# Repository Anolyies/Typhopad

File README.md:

# Typhopad
A Starter Hackpad Project | By Anolyies

**A Short Rant**
I used Solidworks rather than Fusion360, the assembly part of the case was really annoying, I didn't know what to do, and the tutorials online weren't great, but I got it done alright, I think. Also, colors in the images look terible, because I added them last second.

The Schematic / PCB:
-------------------------------
   
*Schematic / Left*                                              | *PCB / Right*

--------------------------------------------------
I wasn't too sure on how to make the PCB. It's my first time using KICad and making a PCB schematic. The routing and pcb itself looks pretty bad, it doesn't use a switch matrix, it's directly wired. I'm not too sure what that means but yeah. I tried to follow the beginner friendly tutorial as close as possible, then added the OLED display and RotaryEncoder, but kind of winged it, as there was no tutorial on how to do those ones. I don't know if this PCB will work, but I hope it will. Lastly, the OLED display area, I'll just directly solder the pins on the OLED display into the holes rather than using a JConnector.

The Assembly:
----------------------------------

---------------------------------------------
This design follows the tutorial really pretty closely with only a few differences, but I think that's fine for a semi-beginner.

I add the PCB with wiring,soldering, and etc... Into the bottom case. 4x M3x16mm screws go through the bottom of the cas, then I use 4x M3x5mx4mm heatset inserts to secure the screws. The add the keycaps and boom done.

Firmware:
----------------------------------
Firmare was not really made by me, it was made primarilly by Chet Gippiti (ChatGPT). I also dont know if it works, so when I get my own board, I'll test and see if it works and fix it if it doesn't.
[Check out the code and setup](./Firmware)

**BOM**
------------------------------------

- 4x Cherry MX Switches
- 4x DSA Keycaps
- 4x M3 Heatset
- 4x M3x16mm Bolts
- 1x XIAO RP2040
- 2x SK6812 MINI Leds
- 1x 1x 0.91" 128x32 OLED Display
- 1x EC11 Rotary encoders
- 1x Case [2 printed parts(Bottom case and Top case)]

##

I don't know how well, or if any of this even works, but regardless, I think I learned a decent bit and did something cool that I've never done before.

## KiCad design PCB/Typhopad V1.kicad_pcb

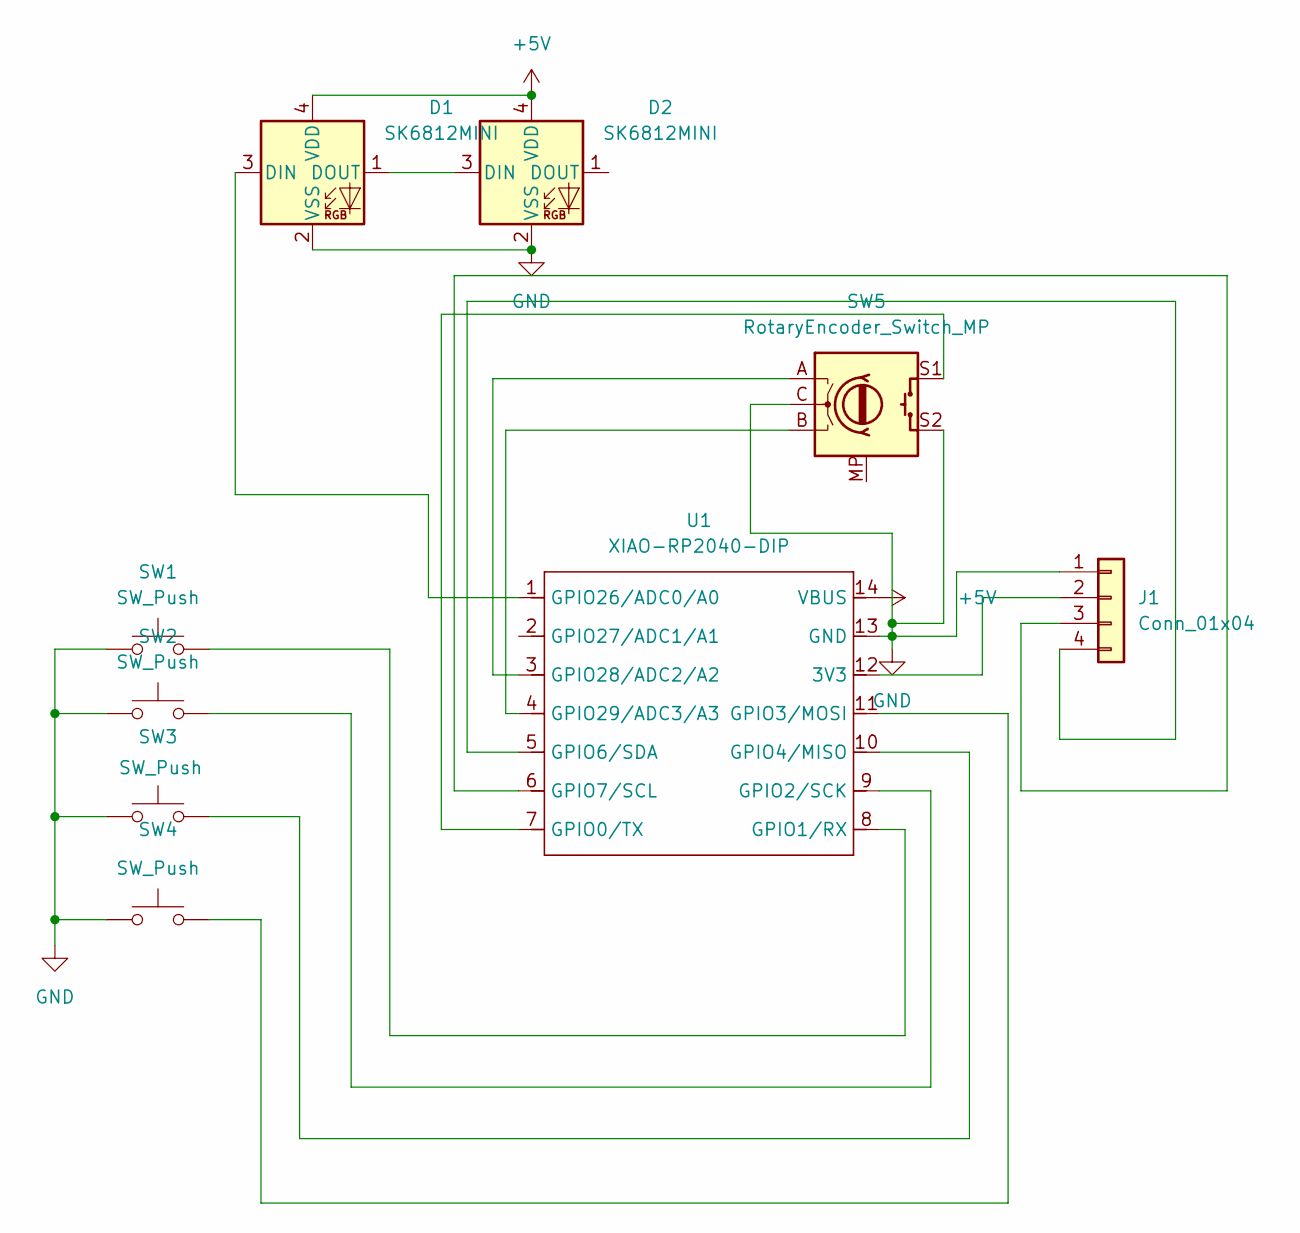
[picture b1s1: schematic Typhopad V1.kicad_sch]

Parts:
D1, D2: SK6812MINI; LED_SK6812MINI_PLCC4_3.5x3.5mm_P1.75mm
J1: Conn_01x04; PinHeader_1x04_P2.54mm_Vertical
SW1, SW2, SW3, SW4: SW_Push; SW_Cherry_MX_1.00u_PCB
SW5: RotaryEncoder_Switch_MP; RotaryEncoder_Alps_EC11E-Switch_Vertical_H20mm_MountingHoles
U1: XIAO-RP2040-DIP

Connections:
+5V: D1.4 (VDD), D2.4 (VDD), U1.14 (VBUS)
GND: D1.2 (VSS), D2.2 (VSS), J1.1, SW1.1, SW2.1, SW3.1, SW4.1, SW5.C, SW5.S2, U1.13 (GND)
unnamed: D1.3 (DIN), U1.1 (GPIO26/ADC0/A0)
unnamed: D1.1 (DOUT), D2.3 (DIN)
unnamed: J1.2, U1.12 (3V3)
unnamed: J1.3, U1.6 (GPIO7/SCL)
unnamed: J1.4, U1.5 (GPIO6/SDA)
unnamed: SW5.S1, U1.7 (GPIO0/TX)
unnamed: SW1.2, U1.8 (GPIO1/RX)
unnamed: SW2.2, U1.9 (GPIO2/SCK)
unnamed: SW4.2, U1.11 (GPIO3/MOSI)
unnamed: SW3.2, U1.10 (GPIO4/MISO)
unnamed: SW5.A, U1.3 (GPIO28/ADC2/A2)
unnamed: SW5.B, U1.4 (GPIO29/ADC3/A3)

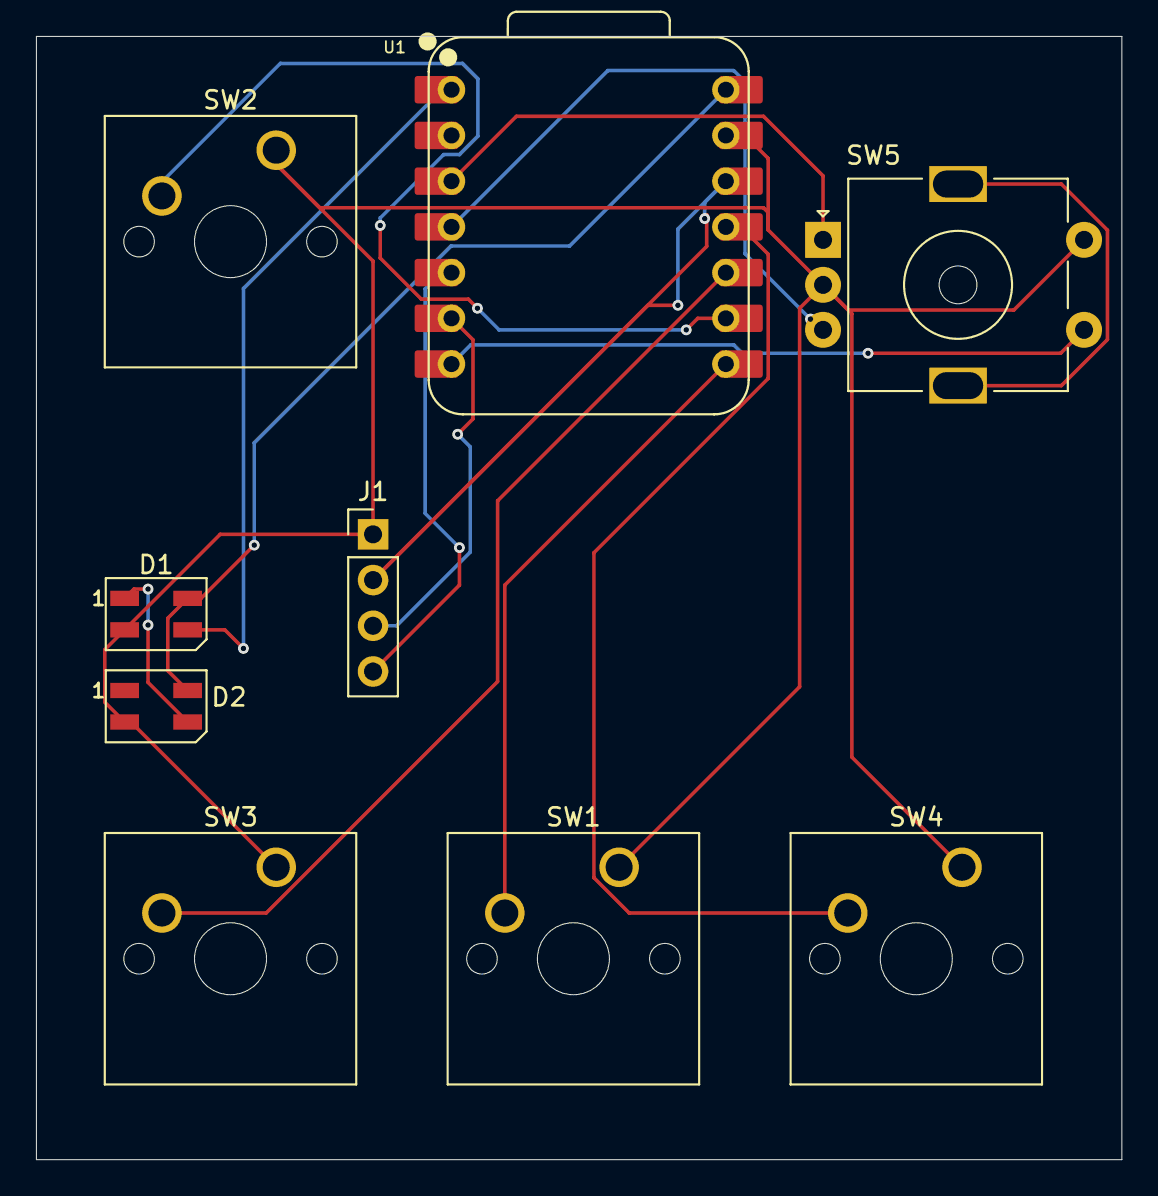
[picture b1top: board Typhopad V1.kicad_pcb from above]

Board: 2 copper layers, 60.3 x 62.4 mm, 9 parts (0 on the bottom side), 14 nets.

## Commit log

2025-11-28 CAD File
2025-11-28 Create CAD
2025-11-28 Full Assembly
2025-11-28 Create A
2025-11-29 Create config.h
    Thank you ChetGippiti
2025-11-29 Create rules.mk
    Thank You ChetGippiti
2025-11-29 Update rules.mk
    Thank You Chet Gippiti
2025-11-29 Update config.h
    Thank You Chet Gippiti!
2025-11-29 Create keyboard.json
    Thank You Chet Gippiti!
2025-11-29 Create keymap.c
    Thank You Chet Gippiti!
2025-11-29 Create None
2025-11-29 Create main.py
    Thank You Chet Gippiti!
2025-11-29 Create README.md
    Thank You Chet Gippiti!
2025-11-29 Create Firmware
2025-11-29 Create s
2025-11-29 Rename s to Firmware
2025-11-29 Update Firmware
2025-11-29 Rename Firmware to Firmware.md
